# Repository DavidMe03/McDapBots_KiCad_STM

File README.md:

# McDap Bots Pedagogical Robot

This project was created as a capstone project for the University of Virginia Department of Electrical and Computer Engineering. Our goal was to create a small robot which could be programmed by students, for use as a teaching aide in an embedded systems course. This repository contains the hardware files specific to the STM adapter board.

**Authors**
- Colby Wise
- Pratik Pandit
- Austen Yun 
- David Merino
- Marc Rosenthal

**Advisors**: Todd DeLong and Adam Barnes 

**Features at a glance**
- 2 motors (PWM controlled), OLED screen (I2C), reflectance sensor (I2C), bump switches (GPIO), Bluetooth (UART), and infrared sensors (ADC)
- battery charging port and battery voltage display (press button to enable)
- support for TI and STM microcontrollers

## What is contained here
STM32 adapter board for the McDap pedalogical robot. Used to reroute the pins of the main board to the STM Nucleo-G071RB

**Bill of Materials Files**

BOM.xlsx contains a list of all the parts needed for the STM Adapter Board.

Digikey_Parts_List.xlsx can be uploaded to Digikey to select the parts needed for one copy of this board.

## How to use this repository
1. Copy the repository locally to your computer
2. Using KiCad 8.0 (or higher version) open the file `AdapterBoard_McDap.kicad_pro`
3. Generate necessary gerber files and order components
4. Follow the provided construction guide to build the robot

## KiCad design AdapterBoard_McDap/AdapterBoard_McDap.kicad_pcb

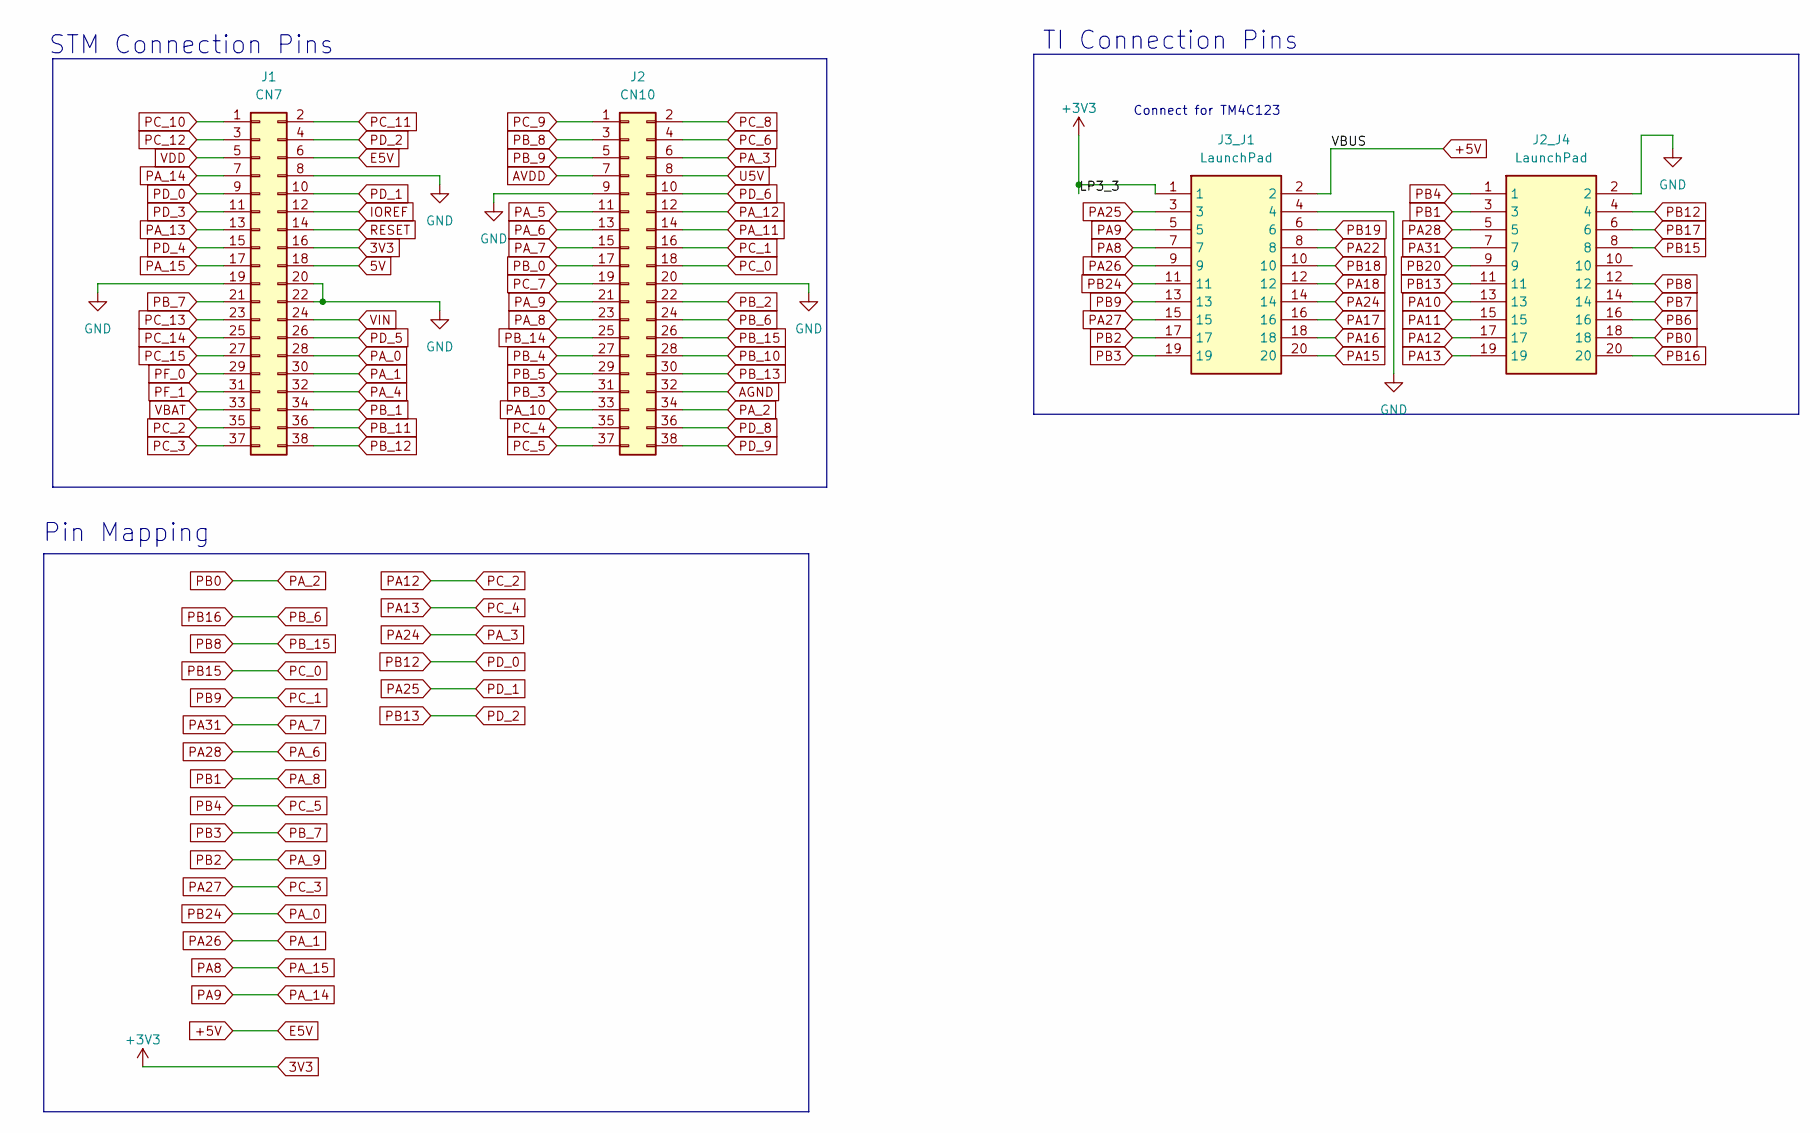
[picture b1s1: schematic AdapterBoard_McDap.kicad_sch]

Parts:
J1: CN7; PinHeader_2x19_P2.54mm_Vertical
J2: CN10; PinHeader_2x19_P2.54mm_Vertical
J2_J4, J3_J1: LaunchPad; PinHeader_2x10_P2.54mm_Vertical; Mouser Part Number 855-M20-8761042P

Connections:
3V3: J1.16, J3_J1.1
5V: J1.18
+5V: J1.6, J3_J1.2
AGND: J2.32
AVDD: J2.7
GND: J1.8, J1.19, J1.20, J1.22, J2.9, J2.20, J2_J4.2, J3_J1.4
IOREF: J1.12
PA8: J1.17, J3_J1.7
PA9: J1.7, J3_J1.5
PA10: J2_J4.13
PA11: J2_J4.15
PA12: J1.35, J2_J4.17
PA13: J2.35, J2_J4.19
PA15: J3_J1.20
PA16: J3_J1.18
PA17: J3_J1.16
PA18: J3_J1.12
PA22: J3_J1.8
PA24: J2.6, J3_J1.14
PA25: J1.10, J3_J1.3
PA26: J1.30, J3_J1.9
PA27: J1.37, J3_J1.15
PA28: J2.13, J2_J4.5
PA31: J2.15, J2_J4.7
PA_0: J1.28, J3_J1.11
PA_2: J2.34, J2_J4.18
PA_4: J1.32
PA_5: J2.11
PA_8: J2.23, J2_J4.3
PA_9: J2.21, J3_J1.17
PA_10: J2.33
PA_11: J2.14
PA_12: J2.12
PA_13: J1.13
PB3: J1.21, J3_J1.19
PB4: J2.37, J2_J4.1
PB6: J2_J4.16
PB7: J2_J4.14
PB8: J2.26, J2_J4.12
PB9: J2.16, J3_J1.13
PB12: J1.9, J2_J4.4
PB13: J1.4, J2_J4.11
PB15: J2.18, J2_J4.8
PB16: J2.24, J2_J4.20
PB17: J2_J4.6
PB18: J3_J1.10
PB19: J3_J1.6
PB20: J2_J4.9
PB_0: J2.17
PB_1: J1.34
PB_2: J2.22
PB_3: J2.31
PB_4: J2.27
PB_5: J2.29
PB_8: J2.3
PB_9: J2.5
PB_10: J2.28
PB_11: J1.36
PB_12: J1.38
PB_13: J2.30
PB_14: J2.25
PC_6: J2.4
PC_7: J2.19
PC_8: J2.2
PC_9: J2.1
PC_10: J1.1
PC_11: J1.2
PC_12: J1.3
PC_13: J1.23
PC_14: J1.25
PC_15: J1.27
PD_3: J1.11
PD_4: J1.15
PD_5: J1.26
PD_6: J2.10
PD_8: J2.36
PD_9: J2.38
PF_0: J1.29
PF_1: J1.31
RESET: J1.14
U5V: J2.8
VBAT: J1.33
VDD: J1.5
VIN: J1.24

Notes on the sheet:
TI Connection Pins
STM Connection Pins
Pin Mapping
Connect for TM4C123

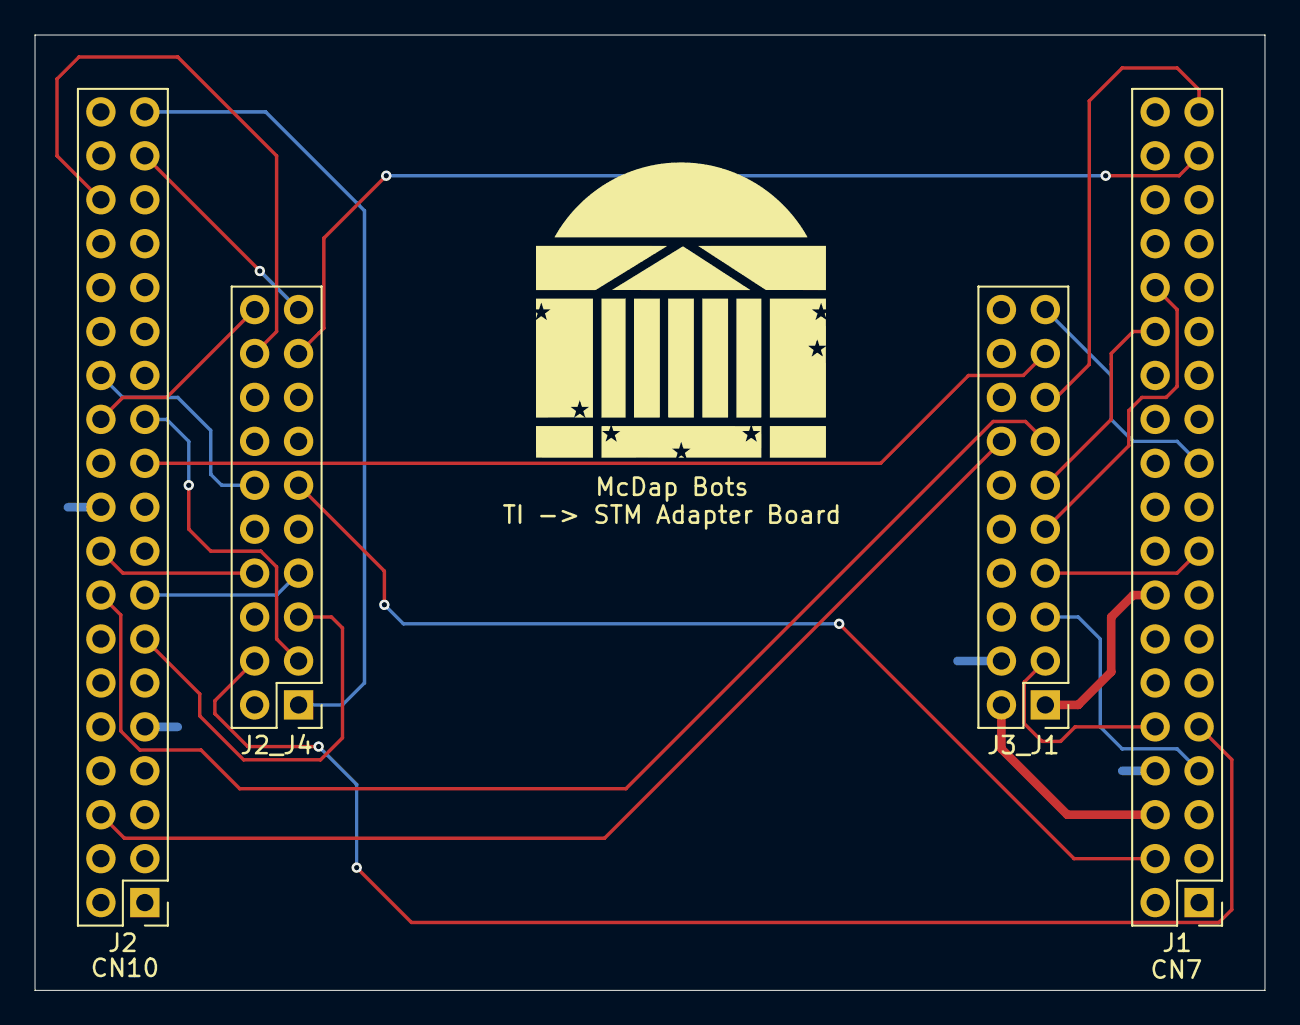
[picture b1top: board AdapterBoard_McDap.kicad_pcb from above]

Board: 2 copper layers, 71.1 x 55.2 mm, 5 parts (0 on the bottom side), 25 nets.

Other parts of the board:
J5: RSLK2; RSLK_Chassis

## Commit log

2025-10-08 First commit of KiCad Project
2025-10-08 Initial Additions to schematic & layout
2025-10-16 Added pinmap connections to schematic; Finished layout for adapter board
2025-10-16 minor track changes
2025-10-16 Fixing some visual stuff
2025-10-16 Added silkscreen image
2025-10-16 Add missing pin connection between TI and STM
2025-10-16 Minor silkscreen improvements
2025-10-21 Generated gerber files
2025-11-07 changed pin mappings
2025-11-11 Generated rev 2 gerber files
2025-12-12 Created README.md
2025-12-18 Added BOM and digikey parts files
2025-12-18 Fix typo in usage instructions
